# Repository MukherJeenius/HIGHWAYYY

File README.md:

It’s a custom-built macro pad designed specifically for League of Legends, letting me hit Q, W, E, and R with mechanical precision.
Whether I'm throwing out skillshots or pulling off a clean combo, this board gives me consistent feedback and control.

Schematic and PCB

# COMPONENTS
4x Cherry MX Switches 4x Cherry MX Switches 
1x XIAO RP2040
Custom 3D Printed Top Case
Custom 3D Printed Bottom Case

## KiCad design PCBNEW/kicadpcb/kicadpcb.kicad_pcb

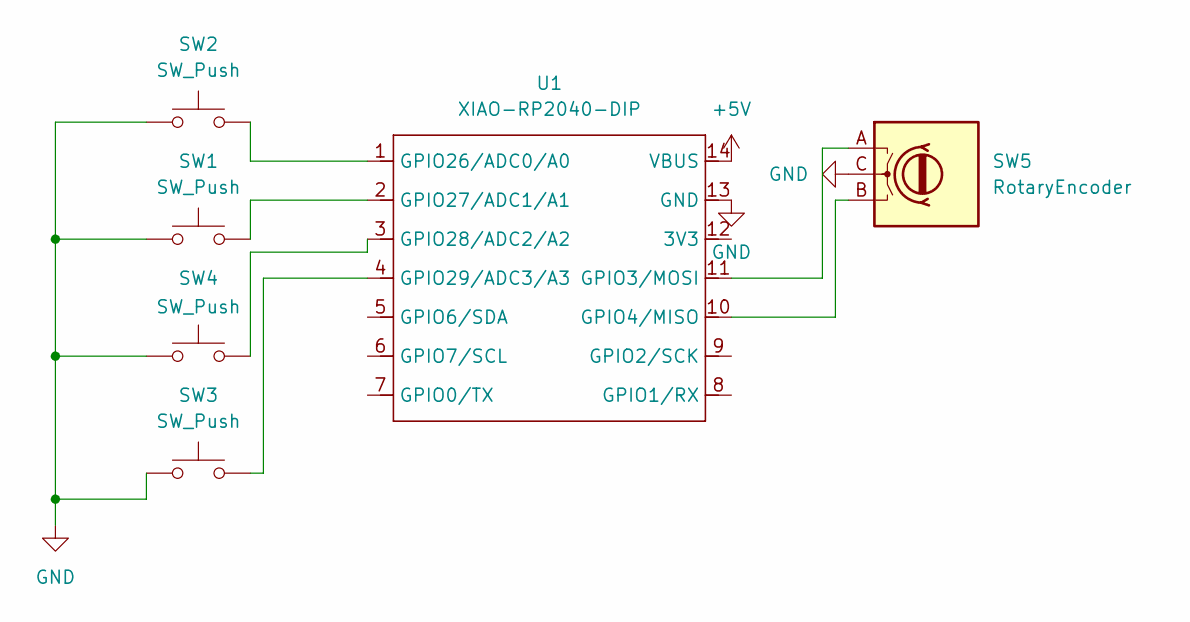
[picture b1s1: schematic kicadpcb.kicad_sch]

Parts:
SW1, SW2, SW3, SW4: SW_Push; SW_Cherry_MX_1.00u_PCB
SW5: RotaryEncoder; RotaryEncoder_Alps_EC11E_Vertical_H20mm
U1: XIAO-RP2040-DIP

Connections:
+5V: U1.14 (VBUS)
GND: SW1.1, SW2.1, SW3.1, SW4.1, SW5.C, U1.13 (GND)
unnamed: SW5.A, U1.11 (GPIO3/MOSI)
unnamed: SW5.B, U1.10 (GPIO4/MISO)
unnamed: SW2.2, U1.1 (GPIO26/ADC0/A0)
unnamed: SW1.2, U1.2 (GPIO27/ADC1/A1)
unnamed: SW4.2, U1.3 (GPIO28/ADC2/A2)
unnamed: SW3.2, U1.4 (GPIO29/ADC3/A3)

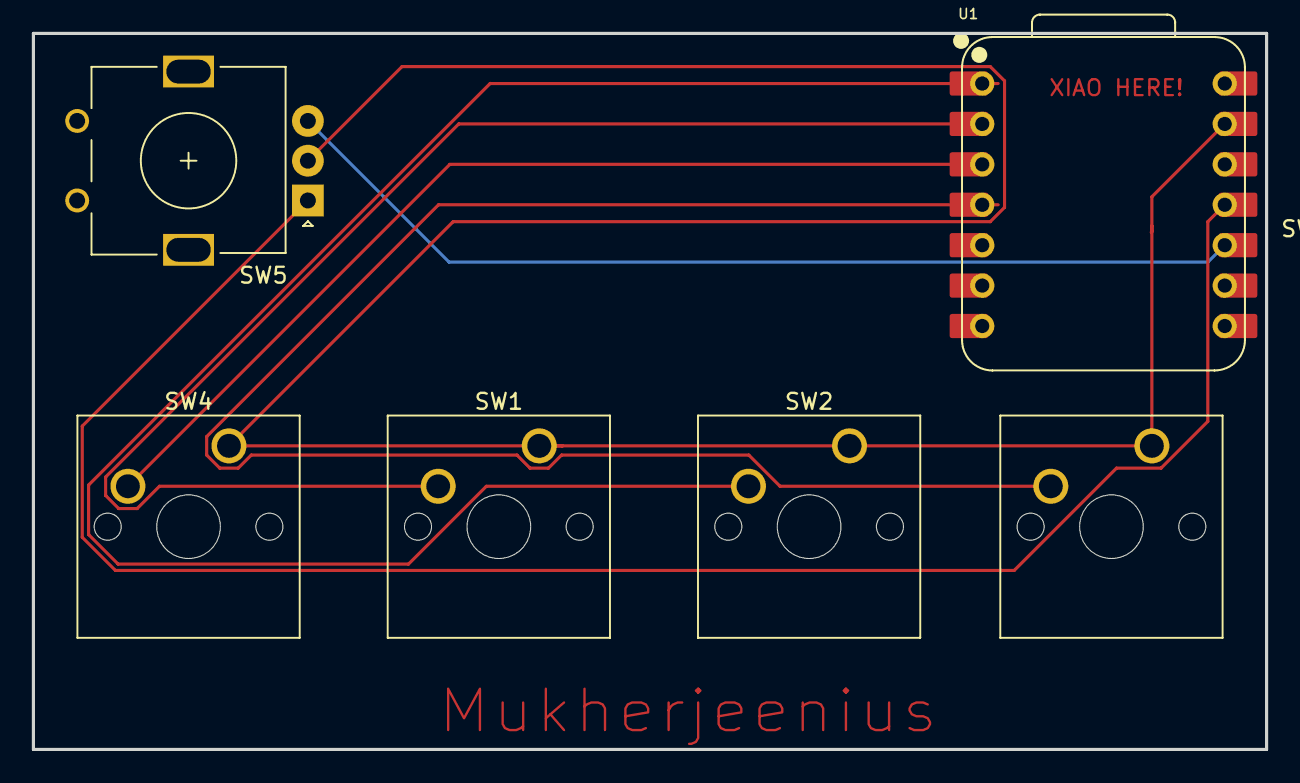
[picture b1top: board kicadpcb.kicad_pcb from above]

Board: 2 copper layers, 77.5 x 45.0 mm, 6 parts (0 on the bottom side), 7 nets.

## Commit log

2025-06-29 main.py
